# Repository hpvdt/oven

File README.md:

# Oven Control System

Our team's generic composite oven controller. Used to maintain a desired two-step curing 
cycle recommended for the majority of our composites. Each step is defined with a target 
temperature, a ramp speed to reach it at (e.g. 2 degC/minute), and hold time at that 
temperature.

The control system is pretty simple, a single K-type thermocouple is used to monitor the 
temperature in the oven, and a simple "ON/OFF" scheme is used to operate the relay that 
controls the power to the heater. Turning ON when below a threshold, and then OFF once 
the upper threshold is surpassed.

User input is handled by a 16 button keypad, with a 20 by 4 character LCD screen used for 
feedback to the user to inform them of their input, and the current state of the oven.

## Code

With the exception of the display code (under "libraries") all the code was written by hand 
in the Arduino IDE. The main firmware is `oven_system` which is written for an Arduino Nano.

It was previously modified to include logging capabilities (`oven_system_with_logging`), 
and another version to operate using the serial interface for input/output in the absence 
of a keybad and/or a screen (`oven_system_no_display`). ***These variants have not been 
maintained to include recent improvements to the main code!***

In addition to the main code, we also prepared unit tests for each piece of hardware we were 
introducing to the system. In these we wrote the code needed to interact with each part as 
well as running some basic tests to exercise both the code and component. These are all in 
the "unit_tests" folder.

## Hardware

The current design is a small circuit board which has the ATmega328P microcontroller and 
the MAX6675 thermocouple chip. The microcontroller is set up to be programmed just like 
an Arduino Nano. Off board is the solid state relay used to regulate the heater, the 5V 
supply, keypad, and screen. This is all housed in a metal case repurposed from a failed 
power supply, with the terminal block used to connect the thermocouple, power, and heater.

The current board was designed in KiCad 6, however my previous versions were designed in 
EAGLE. The most notable differences through iterations are:

- Embedding of the microcontroller and the MAX6675 directly to the main board
- Removal of the logging functionality since it was not used
- The earliest versions were designed to use thermistors instead of a thermocouple
- Previous designs weren't designed to fit in any particular enclosure

## TODO

A small to-do list of future features that could improve the system.

- [ ] Add some system to allow for recovery if power is interrupted
- [ ] Add some system to allow the system to be reset if needed
- [x] Figure out why SPI programming doesn't work if the MAX6675 is connected in any way
    - This was due to the MAX6675 not having a pullup on nCS, so it was active during programming of the ATmega and interfered on the SPI bus.
    - This **should** be revised in future hardware revisions

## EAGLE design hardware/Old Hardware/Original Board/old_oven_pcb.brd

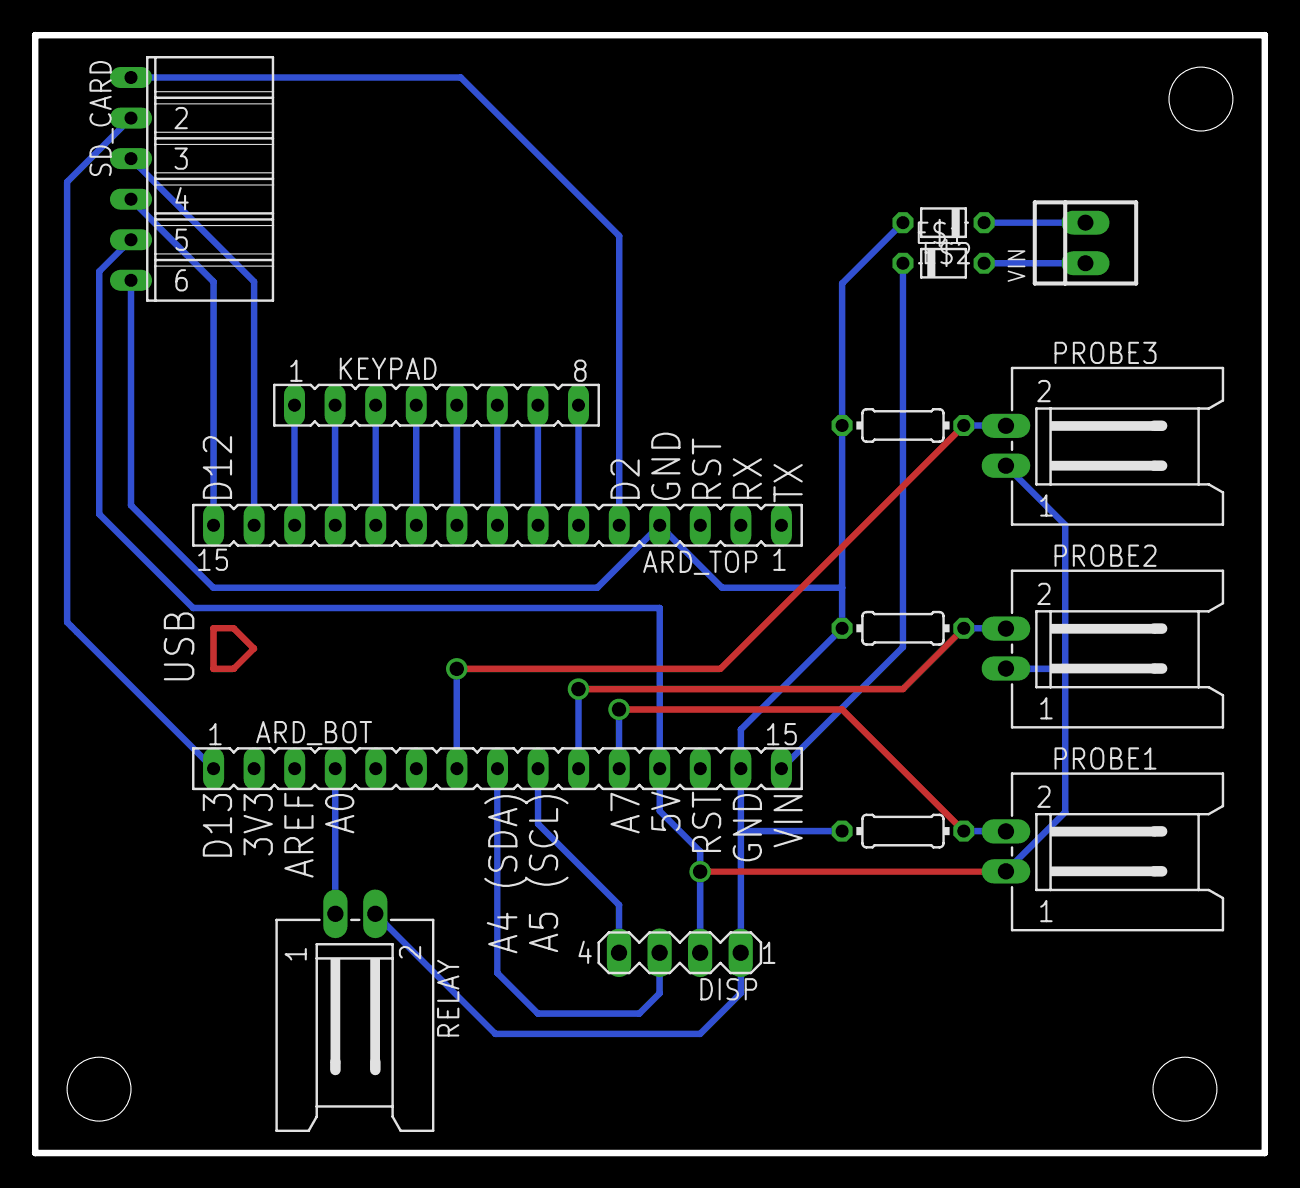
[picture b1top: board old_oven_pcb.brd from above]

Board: 2 copper layers, 77.0 x 70.0 mm, 15 parts (0 on the bottom side), 23 nets.

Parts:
ARD_BOT: FE15
ARD_TOP: FE15
DISP: MA04-1
E$1, E$2: D-5
E$3, E$4, E$6: 10k; 0204/7
KEYPAD: FE08
PROBE1, PROBE2, PROBE3: L02P
RELAY: L02P
SD_CARD: FE06W
VIN: 22-23-2021

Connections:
5V: ARD_BOT.12, DISP.2, PROBE1.1, PROBE2.1, PROBE3.1, SD_CARD.5
D3: ARD_TOP.6, KEYPAD.8
D4: ARD_TOP.7, KEYPAD.7
D5: ARD_TOP.8, KEYPAD.6
D6: ARD_TOP.9, KEYPAD.5
D7: ARD_TOP.10, KEYPAD.4
D8: ARD_TOP.11, KEYPAD.3
D9: ARD_TOP.12, KEYPAD.2
D10: ARD_TOP.5, SD_CARD.1
D13: ARD_BOT.1, SD_CARD.2
GND: ARD_BOT.14, ARD_TOP.4, DISP.1, E$2.A, E$3.2, E$4.2, E$6.2, RELAY.2, SD_CARD.6
PROBE1: ARD_BOT.11, E$4.1, PROBE1.2
PROBE2: ARD_BOT.10, E$3.1, PROBE2.2
PROBE3: ARD_BOT.7, E$6.1, PROBE3.2
RELAY: ARD_BOT.4, RELAY.1
S$1: ARD_TOP.13, KEYPAD.1
S$3: ARD_TOP.15, SD_CARD.4
S$4: ARD_TOP.14, SD_CARD.3
SCL: ARD_BOT.9, DISP.4
SDA: ARD_BOT.8, DISP.3
V+: E$1.A, VIN.1
V-: E$2.C, VIN.2
VIN: ARD_BOT.15, E$1.C

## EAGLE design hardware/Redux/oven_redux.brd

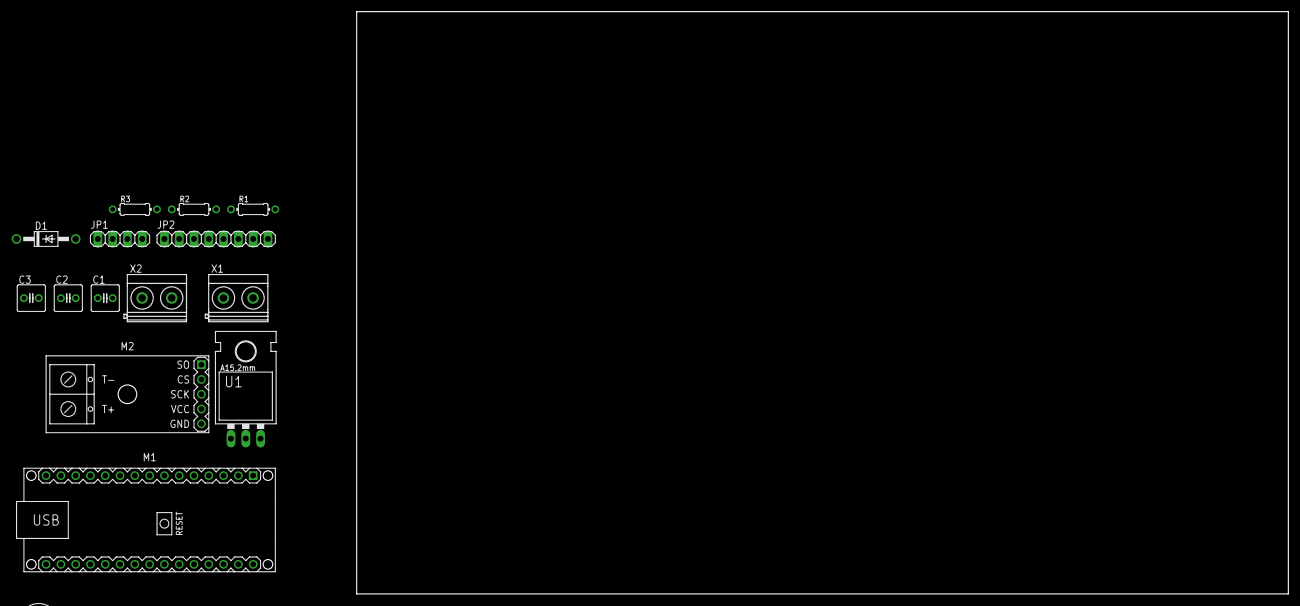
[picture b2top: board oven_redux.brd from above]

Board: 2 copper layers, 160.0 x 100.0 mm, 18 parts (0 on the bottom side), 19 nets, no tracks yet.

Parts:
C1: 0u1; C025-050X050
C2, C3: 1u; C025-050X050
D1: 1N4004; DO41-10
H1, H2, H3, H4: MOUNT-HOLE3.3; 3,3
JP1: DISP; 1X04
JP2: NUMPAD; 1X08
M1: ARDUINO-NANO-3.0
M2: THERMOCOUPLE-MAX6675
R1: 1k; 0204/7
R2: 3k1; 0204/7
R3: 10k; 0204/7
U1: 317TL
X1: RELAY; MKDSN1,5/2-5,08
X2: POWER; MKDSN1,5/2-5,08

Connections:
+5V: C2.1, C3.1, JP1.4, M1.J2.4, M2.VCC, R2.1, U1.2
GND: C1.2, C2.2, C3.2, JP1.1, M1.J1.4, M1.J2.2, M2.GND, R1.2, R3.2, X1.1, X2.1
unnamed: JP2.1, M1.J1.12
unnamed: JP2.2, M1.J1.11
unnamed: JP2.3, M1.J1.10
unnamed: JP2.4, M1.J1.9
unnamed: JP2.5, M1.J1.8
unnamed: JP2.6, M1.J1.7
unnamed: JP2.7, M1.J1.6
unnamed: JP2.8, M1.J1.5
unnamed: JP1.2, M1.J2.7
unnamed: R1.1, R2.2, U1.1
unnamed: C1.1, D1.C, U1.3
unnamed: D1.A, X2.2
unnamed: JP1.3, M1.J2.8
unnamed: M1.J2.9, M2.SCK
unnamed: M1.J2.10, M2.CS
unnamed: M1.J1.13, R3.1, X1.2
unnamed: M1.J2.11, M2.SO

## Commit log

2021-06-07 Upload of hardware files
2021-06-07 Upload of unit tests for parts
2021-06-07 Initial upload of oven system code
2021-06-07 Moved to unit test folder
2021-06-07 Moved ionto unit test folder
2021-06-07 Rename unit_tests/display_test.ino to unit_tests/display_test/display_test.ino
2021-06-07 Moved into unit test folder
2021-06-07 Rename LCD.h to libraries/Newliquidcrystal_1.3.5/LCD.h
2021-06-07 Partial upload of LCD library
2021-06-11 Breaking main file down into seperate files
2021-06-11 Added code to operate using MAX6675
2021-06-15 Accounting for millis() inaccuracy
2022-03-16 Added MAX6675 unit test code
2022-03-16 Reworking hardware folder
2022-03-16 Uploaded reorganized hardware folder
2022-03-16 Accomodate new board design in code
2022-03-16 Added media for readme
2022-03-16 Added images to readme
2022-03-25 Updated oven revision to have buzzer
2023-12-08 Moved code into firmware folder
2023-12-08 Update README.md
    Added cause and remedy for programming issues related to MAX6675 chip
2024-02-14 Changed hardware organisation, updated to KiCad 7
2024-02-14 Started rev 3 project
2024-02-14 Removed unrelated gerbers from rev 3
2024-02-14 Moved Arduino code into a directory
2024-02-14 Removed unneed hardware files
2024-02-14 Updated `.gitignore`s
2024-02-14 Added KiCad `.gitignore`
2024-02-14 Created PlatformIO project for oven
2024-02-14 Tidied up keypad code
    Changed indenting to 4 spaces, made short delays use `delayMicroseconds`, added comments for functions.
2024-02-14 Generalized the temperature code
2024-02-14 Added support for switching between MAX chips
2024-02-14 Added `lcd` dependancy to header
2024-02-14 Fixed logic for second ramp
2024-02-14 Tidied up main code
    Lots of small changes:
    - Made lots of one line control statements single line
    - Changed `fields` to be a two dimensional array for easier reading
    - Changed code to avoid over shooting rather than undershooting (with configurable tolerance)
2024-02-14 Touched up title blocks and rev 3
2024-02-14 Minor touchups for titleblocks
2024-02-14 Removed buzzer that was not present in fabricated boards
2024-02-14 Fixed pin allocations for rev 2 board
2024-02-14 Minor touchups for temperature reading
2024-02-14 Proper masking of MAX6675 status bit
2024-02-14 Reduced scope of some variables
2024-02-14 Added trim for measured inaccuracy of resonator
2024-02-23 Added ability to exit baking
2024-04-05 Added watchdog reset
2024-05-11 Extended watchdog timer to allow reset to be keyed
2024-05-11 Can skip second stage
    Added ability to skip second stage is only a single stage cure is desired by having the second stage temperature lower than the first

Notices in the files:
parts and their libraries:
diy-modules: Released under the Creative Commons Attribution 4.0 International License: http://creativecommons.org/licenses/by/4.0
